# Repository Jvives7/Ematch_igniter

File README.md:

# Ematch_igniter

Devloping ematch igniter circuit

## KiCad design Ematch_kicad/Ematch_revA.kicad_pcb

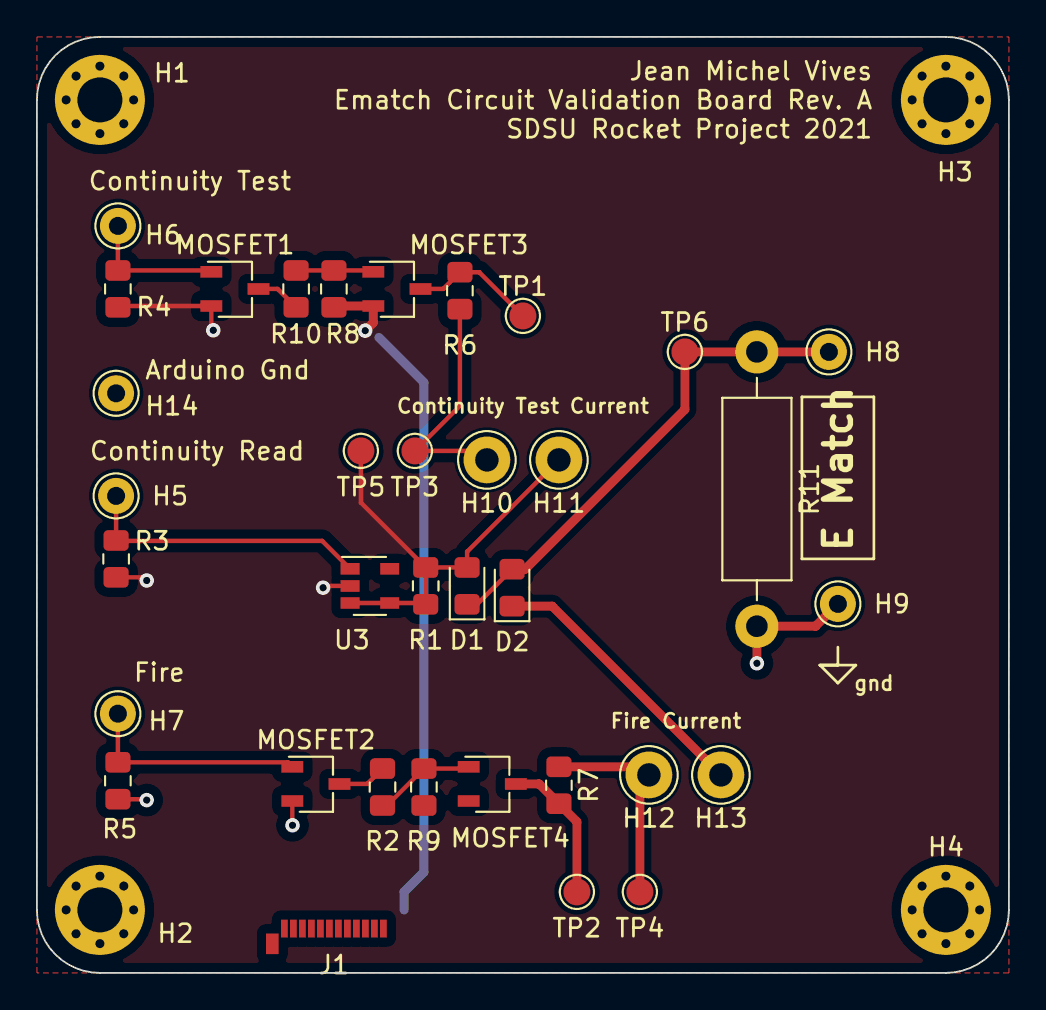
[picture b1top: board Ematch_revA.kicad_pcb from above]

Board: 2 copper layers, 54.0 x 52.0 mm, 39 parts (0 on the bottom side), 16 nets.

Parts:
D1: D; D_0805_2012Metric_Pad1.15x1.40mm_HandSolder
D2: DIODE; D_0805_2012Metric_Pad1.15x1.40mm_HandSolder
H1, H2, H3, H4: MountingHole_Pad; MountingHole_2.5mm_Pad_Via
H5, H6, H7, H8, H9, H14: MountingHole_Pad; Pin_D1.0mm_L10.0mm
H10, H11, H12, H13: MountingHole_Pad; Pin_D1.3mm_L11.0mm
J1: Conn_01x02_Female; USB_C_Plug_Molex_105444
MOSFET1, MOSFET2: IRLML6246TRPBF; TSOT-23
MOSFET3, MOSFET4: IRLML6401TRPBF; TSOT-23
R1: 0.5; R_0805_2012Metric_Pad1.15x1.40mm_HandSolder
R2, R10: 1k; R_0805_2012Metric_Pad1.15x1.40mm_HandSolder
R3, R4, R5: R_Small; R_0805_2012Metric_Pad1.15x1.40mm_HandSolder
R6: 400R; R_0805_2012Metric_Pad1.15x1.40mm_HandSolder
R7: 10R; R_0805_2012Metric_Pad1.15x1.40mm_HandSolder
R8, R9: 10k; R_0805_2012Metric_Pad1.15x1.40mm_HandSolder
R11: R; R_Axial_DIN0411_L9.9mm_D3.6mm_P15.24mm_Horizontal
TP1, TP2, TP3, TP4, TP5, TP6: TestPoint; TestPoint_Pad_D1.5mm
U3: INA138; SOT-23-5

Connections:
+12V: MOSFET3.2, MOSFET4.2, R8.1, R9.1, U3.5
/Continuity_Read: H5.1, R3.1, U3.1
/Continuity_Test: H6.1, MOSFET1.1, R4.1
/Fire: H7.1, MOSFET2.1, R5.1
GND: H1.1, H2.1, H3.1, H4.1, H9.1, H14.1, MOSFET1.2, MOSFET2.2, R3.2, R4.2, R5.2, R11.2, U3.2
unnamed: D1.1, D2.2, H8.1, R11.1, TP6.1
unnamed: D1.2, H11.1, R1.1, R1.2, TP5.1, U3.3, U3.4
unnamed: D2.1, H13.1
unnamed: H10.1, R6.1, TP3.1
unnamed: H12.1, R7.1, TP4.1
unnamed: MOSFET1.3, R10.2
unnamed: MOSFET2.3, R2.2
unnamed: MOSFET3.1, R8.2, R10.1
unnamed: MOSFET3.3, R6.2, TP1.1
unnamed: MOSFET4.1, R2.1, R9.2
unnamed: MOSFET4.3, R7.2, TP2.1

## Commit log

2021-07-18 Adding kicad files
2021-07-18 organized files
2021-07-19 Added discrete switch
2021-07-20 Added pcb layout and improved schematic
2021-08-02 added amatch requirements text
